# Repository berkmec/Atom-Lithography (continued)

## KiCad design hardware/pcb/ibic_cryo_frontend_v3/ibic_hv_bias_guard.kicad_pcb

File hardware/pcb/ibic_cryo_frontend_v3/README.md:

# IBIC Cryo Front-End v3 — Split 3-PCB KiCad 8 Kit & Real 100 K `ngspice` Verification

**BOM Coverage:** `S3.1-01`, `S3.1-02`, `S3.2-01`, `S3.2-02`, `S3.2-03`, `S3.2-04`, `S3.2-05`, `S3.2-06`, `S3.3-03`  
**Epistemic Status:** `M0/M1_DESIGN_ONLY` — `no_lab_measurement=true`, `no_physical_fab=true`, `iec61508_certified=false`, `semi_s2_certified=false`. All active semiconductors are `{Aday-COTS}` candidate parts.

## 1. Physically Split 3-PCB Kit (100% Physically Routed Pad-to-Pad; Closing #281 & #327)

Replaces the pre-layout monolithic netlist (`src/board/detector_frontend.*`, preserved read-only for v7.2 hash parity) with 3 physically split KiCad 8 boards verified by strict S-expression parsing, reconstructive schematic-to-PCB ERC, full geometric + pad-segment-via-zone Union-Find connectivity DRC (`0` unconnected items, `0` dangling tracks), controlled-impedance `Z0` (`±5%`), IPC-2221/IEC-61010 HV rules, real `ngspice-47`, and independent Python MNA:

| Board Slug | BOM IDs | Temp / Env | Stackup & Size | Comps / Nets | Routed / Unconn / Dangling | Segs / Vias | ERC / DRC | Key Features |
| :--- | :--- | :--- | :--- | :---: | :---: | :---: | :---: | :--- |
| `ibic_cold_csa_100k` | `S3.2-01, S3.1-01/02, S3.2-04/05` | `100 K` UHV (`10⁻⁹ mbar`) | 4L Rogers RO4350B (`ε_r=3.48`), `125×105 mm` | `130 / 56` | **`56/56` / `0` / `0`** | `725 / 225` | **`0 / 0`** | 8× `LTC6268IS8` CSA (exact S8 pinout: `1:~SHDN, 2:V+, 3:OUT, 4:V-, 5/8:GUARD_DRV, 6:-IN, 7:+IN`) + `0805` cryo thin-film `1 GΩ` `RF`, extended `In1/In2` keepouts (`x=34.0..55.2 mm`) & active `U_GRD_BOOT` guard follower (no `100 nF` AC-short), `G=+2` `50 Ω` coax drivers (`Z0=50.00 Ω`) |
| `ibic_warm_shaper_300k` | `S3.2-02, S3.2-06, S3.3-03` | `300 K` EMI Chassis | 4L Isola FR408HR (`ε_r=3.66`), `185×135 mm` | `217 / 116` | **`116/116` / `0` / `0`** | `1,373 / 350` | **`0 / 0`** | 16× `ADA4817-1ARDZ` (`SOIC-8-1EP`: `1:FB, 8:PD=VCCA, 9:EP=VSSA`), 8× `TLV3501AIDBVR` (exact TI SBOS321 DBV: `1:-IN, 2:V-, 3:+IN, 4:V+, 5:OUT, 6:SHDN=DGND`), 5× `MSOP-12-1EP` `LT3045EMSE` (`EP=GND`) / `LT3094EMSE` (`EP=VIN_N`), 100% `F.Cu` `50 Ω` `SHP_ADC`/`COUNT_HIT`/`COAX_IN` over solid `In1.Cu` `AGND`/`DGND` (`0` `B.Cu` `50 Ω` segments) |
| `ibic_hv_bias_guard` | `S3.2-03, S3.1-01/02` | `300 K` HV / Guard | 4L Rogers RO4350B (`ε_r=3.48`), `110×75 mm` | `38 / 21` | **`21/21` / `0` / `0`** | `170 / 32` | **`0 / 0`** | 3-stage RC `0–100 V` HV filter (`3× 10 kΩ / 1.0 µF` 200 V), extended `2.5×61 mm` milled `Edge.Cuts` air-slot enclosing `RHV_DIV_TOP`, non-chopper `AD8675ARZ` driven guard buffer + `100:1` HV sense monitor |

## 2. Real `ngspice-47` & Independent MNA Verification (`ibic_cryo_chain_100k.cir`)

Executed natively with `ngspice-47 -b` (zero PSpice `VALUE={}` / `PARAMS:` syntax, exit code `0`, `0` errors, `0` warnings) using `.temp -173.15` (`100 K`) on the cold CSA stage (with active guard bootstrap follower, `0805` thin-film `RF` parasitic C, and `±2.5 V` supply-rail saturation clamps) and per-resistor `temp=26.85` (`300 K`) on the warm ex-vacuum shaper & HV filter:

| Metric | `ngspice-47` Measured | Independent Python MNA / Exp127 Ref | Target / Spec | Status |
| :--- | :---: | :---: | :---: | :---: |
| Peak AC Transimpedance `Z_peak` | `647.44 MΩ` (`@ 7.34 kHz`) | MNA `647.44 MΩ` (`0.0001%` diff) | `< 1%` MNA parity | **PASS** |
| `5 keV ³¹P⁺` Shaper Peak `V_peak` (`341.7 e⁻`) | `10.834 mV` (`197.9 mV/fC`) | Exp127 `10.917 mV` | `10–12 mV` | **PASS** |
| `5 keV` Peaking Time `t_peak` | `1225.6 ns` (`1.226 µs`) | Exp127 `1218.4 ns` | `≈ 1.2 µs` | **PASS** |
| Buffered FMC PHA ADC Tap `V_adc` | `10.780 mV` | `0.50%` tracking vs `V_peak` | `< 2%` tracking | **PASS** |
| Integrated Noise `ENC` (`10 Hz – 50 MHz`) | **`27.94 e⁻ rms`** | Active guard bootstrap + `300 K` warm shaper & `50 Ω` coax link | `≤ 35 e⁻` | **PASS** |
| `TLV3501` Comparator `COUNT_HIT` | `3.251 V`, `5.20 µs` pulse (`0 V` DC baseline, `SHDN=DGND`) | `V_thr = 4.23 mV`, `3.3 mV` hys | Clean trigger & reset | **PASS** |
| `S3.2-03` 3-Stage HV Filter `@ 100 kHz` | **`-227.86 dB`** (w/ `100 mΩ` ESR, `2 nH` ESL) | MNA `-227.86 dB` (`0.001 dB` diff) | `> 100 dB` (`< -100 dB`) | **PASS** |
| `S3.2-03` HV Filter Integrated Thermal Noise | **`0.142 µVrms`** | — | `< 10 µVrms` | **PASS** |
| Cold CSA `CSA_SUM` Stray Capacitance Budget | `0.109 pF` active bootstrapped (`0.775 pF` passive ref) | `In1/In2` keepout `x=34.0..55.2 mm` | `< 0.15 pF` | **PASS** |

## 3. Reproducibility

```bash
PYTHONPATH=.:src python -B hardware/pcb/ibic_cryo_frontend_v3/build_ibic_v3.py
PYTHONPATH=.:src pytest tests/test_pcb_kernel_and_ibic.py -v -p no:cacheprovider
```

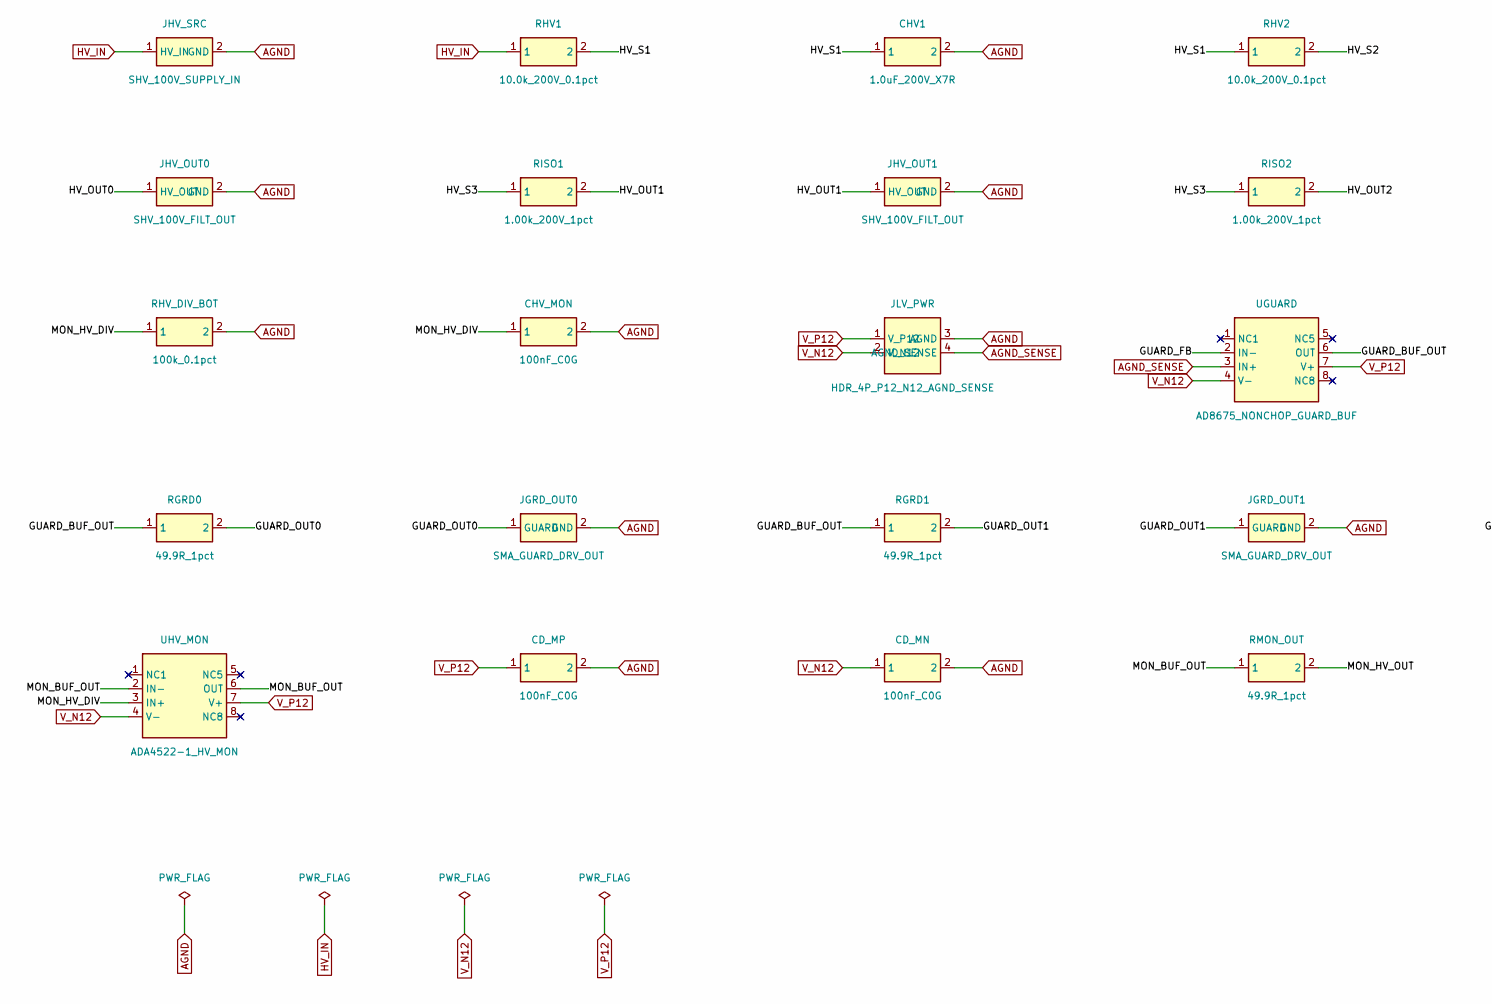
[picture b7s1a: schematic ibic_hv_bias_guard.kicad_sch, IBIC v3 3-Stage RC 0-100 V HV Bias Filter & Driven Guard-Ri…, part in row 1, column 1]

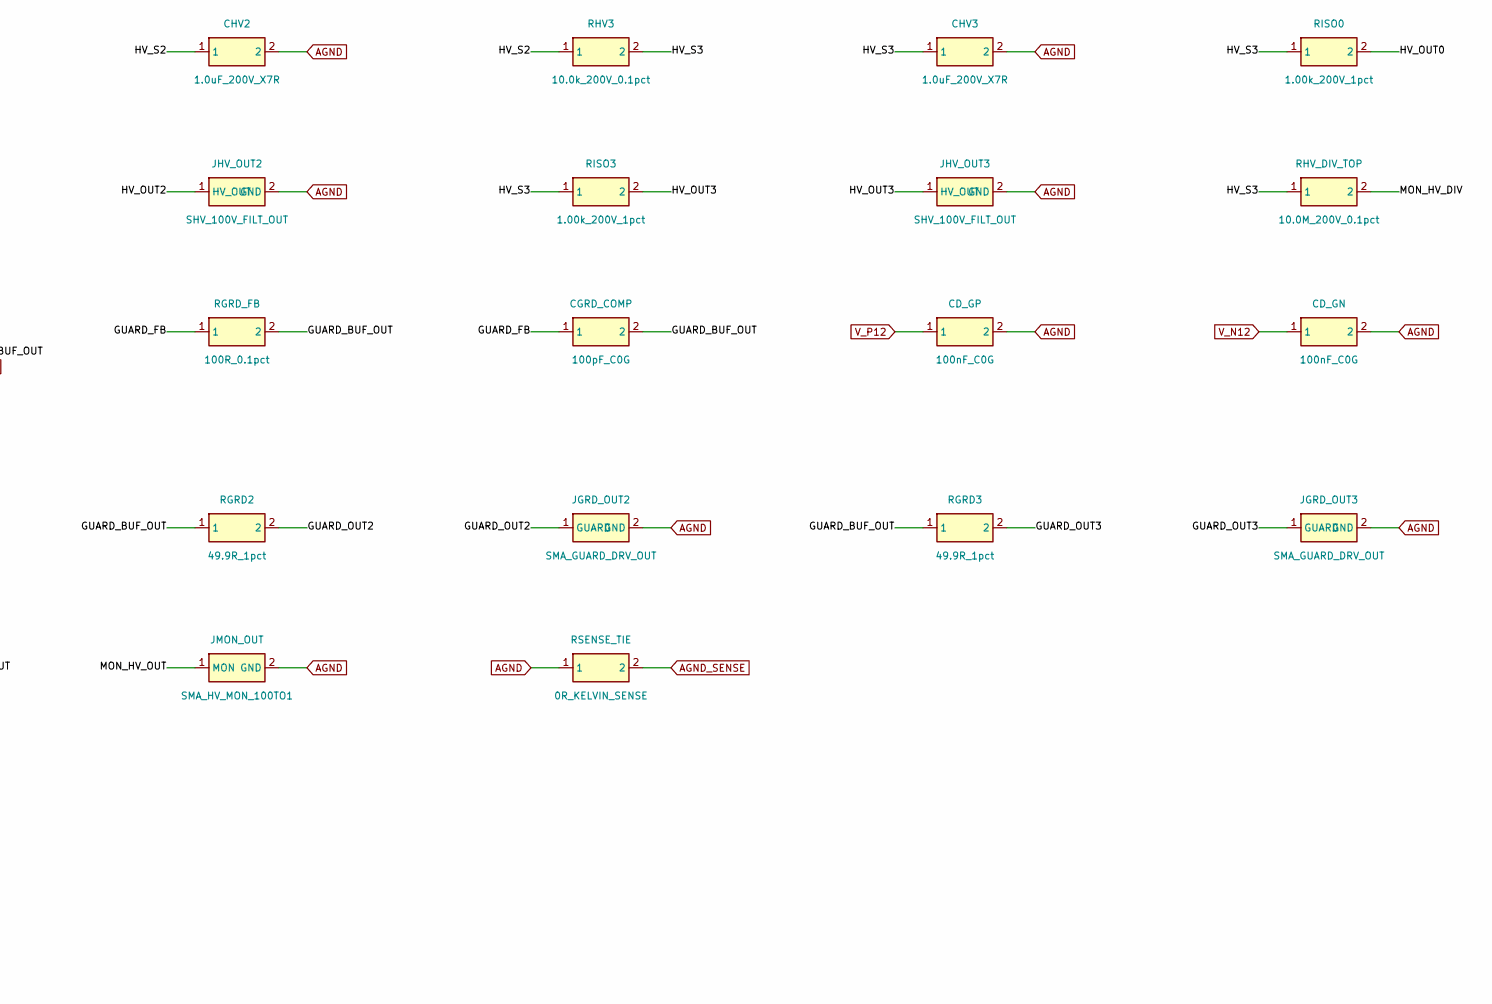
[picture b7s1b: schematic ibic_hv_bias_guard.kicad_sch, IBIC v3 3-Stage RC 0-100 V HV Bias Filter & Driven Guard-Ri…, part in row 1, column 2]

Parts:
CD_GN: 100nF_C0G; C_0603_1608Metric; MPN 100nF_C0G
CD_GP: 100nF_C0G; C_0603_1608Metric; MPN 100nF_C0G
CD_MN: 100nF_C0G; C_0603_1608Metric; MPN 100nF_C0G
CD_MP: 100nF_C0G; C_0603_1608Metric; MPN 100nF_C0G
CGRD_COMP: 100pF_C0G; C_0603_1608Metric; MPN 100pF_C0G
CHV1, CHV2, CHV3: 1.0uF_200V_X7R; C_1210_3225Metric; MPN 1.0uF_200V_X7R
CHV_MON: 100nF_C0G; C_0603_1608Metric; MPN 100nF_C0G
JGRD_OUT0, JGRD_OUT1, JGRD_OUT2, JGRD_OUT3: SMA_GUARD_DRV_OUT; SMA_EdgeMount; MPN SMA_GUARD_DRV_OUT
JHV_OUT0, JHV_OUT1, JHV_OUT2, JHV_OUT3: SHV_100V_FILT_OUT; SHV_Amphenol_HV; MPN SHV_100V_FILT_OUT
JHV_SRC: SHV_100V_SUPPLY_IN; SHV_Amphenol_HV; MPN SHV_100V_SUPPLY_IN
JLV_PWR: HDR_4P_P12_N12_AGND_SENSE; HDR_1x4_2.54mm; MPN HDR_4P_P12_N12_AGND_SENSE
JMON_OUT: SMA_HV_MON_100TO1; SMA_EdgeMount; MPN SMA_HV_MON_100TO1
RGRD0, RGRD1, RGRD2, RGRD3: 49.9R_1pct; R_0603_1608Metric; MPN 49.9R_1pct
RGRD_FB: 100R_0.1pct; R_0603_1608Metric; MPN 100R_0.1pct
RHV1, RHV2, RHV3: 10.0k_200V_0.1pct; R_1206_3216Metric; MPN 10.0k_200V_0.1pct
RHV_DIV_BOT: 100k_0.1pct; R_0805_2012Metric; MPN 100k_0.1pct
RHV_DIV_TOP: 10.0M_200V_0.1pct; R_2512_6332Metric; MPN 10.0M_200V_0.1pct
RISO0, RISO1, RISO2, RISO3: 1.00k_200V_1pct; R_1206_3216Metric; MPN 1.00k_200V_1pct
RMON_OUT: 49.9R_1pct; R_0603_1608Metric; MPN 49.9R_1pct
RSENSE_TIE: 0R_KELVIN_SENSE; R_0603_1608Metric; MPN 0R_KELVIN_SENSE
UGUARD: AD8675_NONCHOP_GUARD_BUF; SOIC-8_3.9x4.9mm_P1.27mm; MPN AD8675ARZ
UHV_MON: ADA4522-1_HV_MON; SOIC-8_3.9x4.9mm_P1.27mm; MPN ADA4522-1ARZ

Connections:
AGND: CD_GN.2, CD_GP.2, CD_MN.2, CD_MP.2, CHV1.2, CHV2.2, CHV3.2, CHV_MON.2, JGRD_OUT0.2 (GND), JGRD_OUT1.2 (GND), JGRD_OUT2.2 (GND), JGRD_OUT3.2 (GND), JHV_OUT0.2 (GND), JHV_OUT1.2 (GND), JHV_OUT2.2 (GND), JHV_OUT3.2 (GND), JHV_SRC.2 (GND), JLV_PWR.3 (AGND), JMON_OUT.2 (GND), RHV_DIV_BOT.2, RSENSE_TIE.1
AGND_SENSE: JLV_PWR.4 (AGND_SENSE), RSENSE_TIE.2, UGUARD.3 (IN+)
GUARD_BUF_OUT: CGRD_COMP.2, RGRD0.1, RGRD1.1, RGRD2.1, RGRD3.1, RGRD_FB.2, UGUARD.6 (OUT)
GUARD_FB: CGRD_COMP.1, RGRD_FB.1, UGUARD.2 (IN-)
GUARD_OUT0: JGRD_OUT0.1 (GUARD), RGRD0.2
GUARD_OUT1: JGRD_OUT1.1 (GUARD), RGRD1.2
GUARD_OUT2: JGRD_OUT2.1 (GUARD), RGRD2.2
GUARD_OUT3: JGRD_OUT3.1 (GUARD), RGRD3.2
HV_IN: JHV_SRC.1 (HV_IN), RHV1.1
HV_OUT0: JHV_OUT0.1 (HV_OUT), RISO0.2
HV_OUT1: JHV_OUT1.1 (HV_OUT), RISO1.2
HV_OUT2: JHV_OUT2.1 (HV_OUT), RISO2.2
HV_OUT3: JHV_OUT3.1 (HV_OUT), RISO3.2
HV_S1: CHV1.1, RHV1.2, RHV2.1
HV_S2: CHV2.1, RHV2.2, RHV3.1
HV_S3: CHV3.1, RHV3.2, RHV_DIV_TOP.1, RISO0.1, RISO1.1, RISO2.1, RISO3.1
MON_BUF_OUT: RMON_OUT.1, UHV_MON.2 (IN-), UHV_MON.6 (OUT)
MON_HV_DIV: CHV_MON.1, RHV_DIV_BOT.1, RHV_DIV_TOP.2, UHV_MON.3 (IN+)
MON_HV_OUT: JMON_OUT.1 (MON), RMON_OUT.2
V_N12: CD_GN.1, CD_MN.1, JLV_PWR.2 (V_N12), UGUARD.4 (V-), UHV_MON.4 (V-)
V_P12: CD_GP.1, CD_MP.1, JLV_PWR.1 (V_P12), UGUARD.7 (V+), UHV_MON.7 (V+)

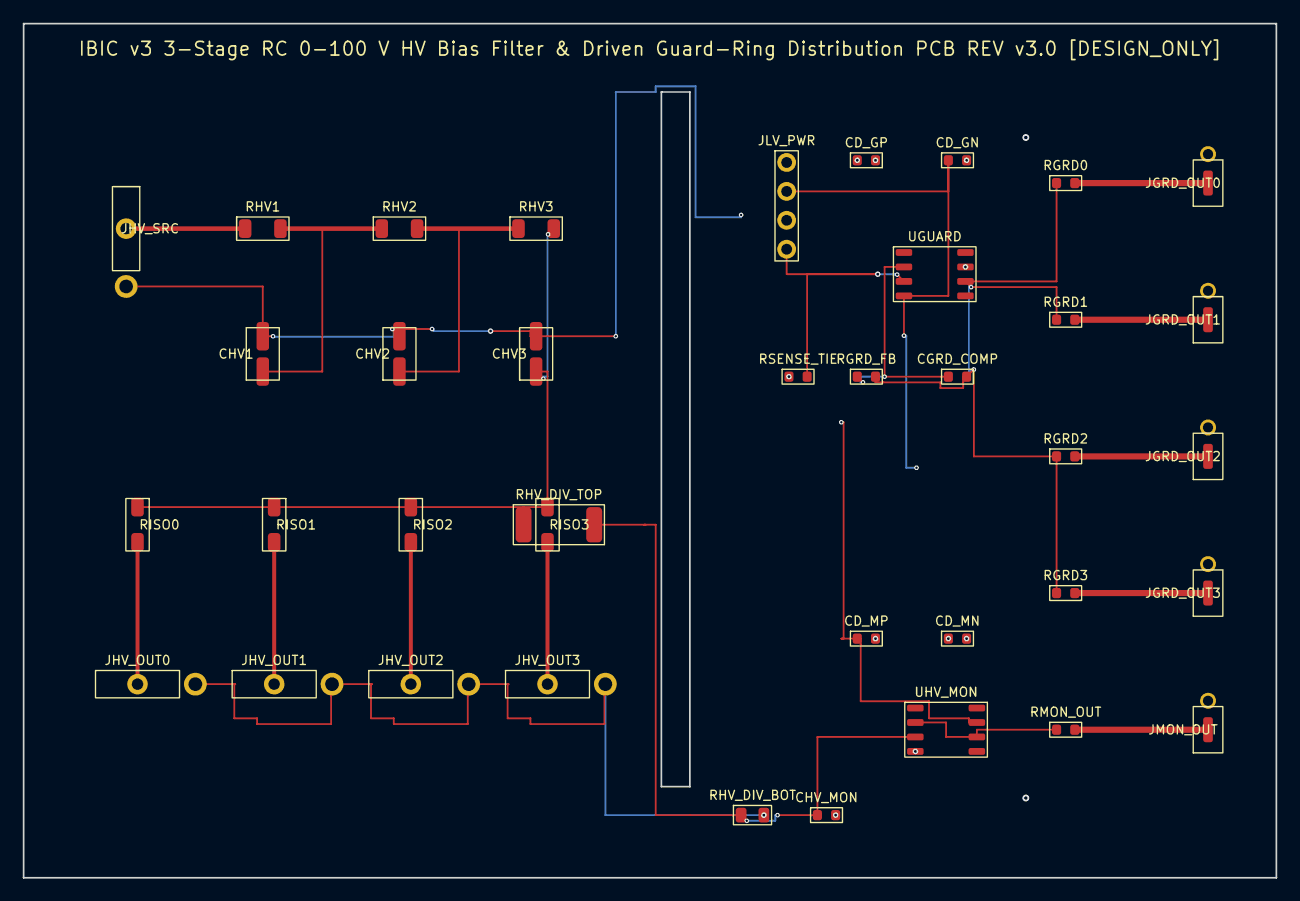
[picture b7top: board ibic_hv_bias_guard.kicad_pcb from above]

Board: 4 copper layers, 110.0 x 75.0 mm, 38 parts (0 on the bottom side), 21 nets.

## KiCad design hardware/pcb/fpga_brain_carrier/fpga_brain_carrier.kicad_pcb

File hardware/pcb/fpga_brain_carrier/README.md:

# FPGA Brain Carrier PCB (`XC7K325T-2FFG900` + `ZU48DR` 2U Rack ICD) & Live `ngspice-47` PDN Verification

**BOM Coverage:** `S3.3-01`, `S3.3-02`, `S3.3-04`, `S1.4-03`, `S4.5-03`, `S6.9-04`, plus `S6.11-01` (`ZU48DR` 2U Rack ICD Ref), `S3.3-03` (`FMC HPC` ADC port), `S7.4-01` (`10 MHz` Rb), `S7.4-02` (White Rabbit trigger).  
**Epistemic Status:** `M0/M1_DESIGN_ONLY` — `no_lab_measurement=true`, `no_physical_fab=true`, `iec61508_certified=false`, `semi_s2_certified=false`. All active semiconductors are `{Aday-COTS}` candidates.

## 1. Yosys-Grounded FPGA Sizing & `ZU48DR` 2U Rack ICD

Directly sized to real Yosys pre-P&R cell counts (`results/exp149_*/yosys_*_stat.json` and `results/stage2_rtl_verification/yosys_xc7_stat.json`):

| RTL Target / Device | LUTs | FFs | BRAM (`BRAM36-eq`) | DSP / MULT | Notes |
| :--- | ---: | ---: | ---: | ---: | :--- |
| `boed_q16_core` (`ecp5` Yosys) | `3,871` | `4,448` | `12 DP16KD` (`6.0`) | `106 MULT18X18D` | Exceeds `LFE5U-45F` (72 DSP) |
| `boed_q16_core` (`xc7` Yosys) | `5,467` | `3,080` | `12 RAMB18E1` (`6.0`) | `99 DSP48E1` | Single-channel BOED core |
| `boed_top_16ch` (`xcup` Yosys) | `102,886` | `59,157` | `192 RAMB18E2` (`96.0`) | `1,584 DSP48E2` | `24.2%` LUT / `37.1%` DSP on `ZU48DR` |
| `fpga_top_machine_ctrl` (`xc7`, BOED + all 6 controllers) | `14,252` | `10,517` | `12 RAMB18E1` (`6.0`) | `124 DSP48E1` | Full unified control brain |
| **Carrier `XC7K325T-2FFG900` Capacity** | **`203,800`** (`14.3×`) | **`407,600`** (`38.8×`) | **`445`** (`74.2×`) | **`840`** (**`6.77×`**) | **`> 4×` headroom across all resources** |
| **`S6.11-01` `ZU48DR` 2U Rack ICD Ref** | `2× XCZU48DR-2FFVG1517E` | `32` Direct-RF chains | `87.96 W` @ `300 K` (`0 W` cryo) | `250 MHz` (`2.336 µs`/step) | `482.6×520×88.9 mm`, `11.50 kg` |

## 2. 8-Layer Isola FR408HR Board Architecture (`fpga_brain_carrier.{kicad_sch,kicad_pcb}`)

- **Dimensions & Stackup:** `230 × 170 mm`, **`8` copper layers** (`SIG1-GND-SIG2-PWR-GND-SIG3-GND-SIG4`), `1.534 mm` total thickness, Isola FR408HR (`ε_r = 3.66`, `tanδ = 0.0092`). `In3.Cu` (`VCCINT_1V0` PWR) and `In4.Cu` (`GND2`) use `2 oz` (`0.070 mm`) copper over a `0.100 mm` thin core for low planar spreading inductance.
- **Controlled Impedance (`104 / 104` DRC checks PASS across all routed segments, `±5%`):**
  - `50 Ω SE` microstrip (`F.Cu`/`B.Cu`): `w = 0.2500 mm` → `Z0 = 50.00 Ω` on `10 MHz` Rb & White Rabbit SMA inputs.
  - `50 Ω SE` stripline (`In2.Cu`/`In5.Cu`): `w = 0.1726 mm` → `Z0 = 50.00 Ω` on `DDR4 DQ0..DQ3`.
  - `100 Ω diff` edge-coupled microstrip (`w = 0.2096 mm`, `s = 0.22 mm` → `Z_diff = 100.00 Ω`) & stripline (`In2.Cu`/`In5.Cu`, `w = 0.1421 mm`, `s = 0.22 mm` → `Z_diff = 100.00 Ω`): coupled `250/100/125 MHz` LVDS clocks with `B.Cu` backside via-in-pad `100 Ω` termination beneath `XC7K325T`, planar fly-by `DDR4 CK`, `FMC HPC` ADC lanes, isolated IBIC/Blanker LVDS ports, and `1000BASE-T` MDI pairs.
- **Subsystems:** `12 V` protected bus → `LM3880` power sequencer → `TPS546D24A` (`1.0 V VCCINT @ 15 A` + `64`-cap 5-decade PDN bank), `1.8 V`, `1.2 V DDR4 + 0.6 V TPS51200 VTT`, `2.5 V LVDS`, `3.3 V IO`, `2× LT3045` (`1.0 V/1.2 V` MGT); `LMK04828` dual-loop jitter cleaner + `CVHD-950` `100 MHz` VCXO; `2 GB` DDR4 (`2× MT40A512M16LY`), `256 Mb` QSPI NOR (`MT25QU256ABA`); `FMC HPC` (`ASP-134488-01`); `4×` isolated LVDS/SPI ports (`ADN4654`/`ADuM141D`: IBIC, Blanker, HV-DAC, AOM/Pyro + `1oo2D` Interlock); `DP83867IR` `1000BASE-T` GbE; `FT232HL` USB-UART; `14-pin` JTAG.
- **Strict EDA & Physical Copper Connectivity Verification:** `139` components, `126` nets, **`routed = 126 / 126` (`100%` pad-to-pad)**, **`unconnected_items = 0`**, **`track_dangling_count = 0`**, `1,625` copper segments, `468` vias, **`0` ERC errors**, **`0` DRC errors**, `SCH ↔ PCB` netlist parity PASS.

## 3. Live `ngspice-47` PDN AC Impedance & `5 A` Transient Verification (`fpga_pdn_1v0.cir`)

Executed natively with `ngspice-47 -b` (exit `0`, `0` errors, `0` warnings) modeling realistic VRM closed-loop impedance (`1.0 mΩ`, `14 nH`), 5-decade bulk+MLCC ESR/ESL (`4× 470 µF`, `8× 47 µF`, `12× 4.7 µF`, `16× 470 nF`, `24× 100 nF`), 2 oz plane spreading inductance, and `XC7K325T` FFG900 package/die capacitance:

| Metric | `ngspice-47` Measured | Independent Python MNA | Target / Spec | Status |
| :--- | :---: | :---: | :---: | :---: |
| Peak `|Z_PDN(f)|` (`100 Hz – 20 MHz`) | **`4.1604 mΩ`** (`@ 30.43 kHz`) | `4.1604 mΩ` (`0.0002%` diff) | `< 10 mΩ` | **PASS** |
| `|Z_PDN|` at `100 Hz` / `10 kHz` / `1 MHz` | `2.000` / `2.366` / `1.782 mΩ` | `2.000` / `2.366` / `1.782 mΩ` | `< 10 mΩ` | **PASS** |
| `|Z_PDN|` at `10 MHz` / `20 MHz` | `2.914` / **`3.210 mΩ`** | `2.913` / `3.209 mΩ` | `< 10 mΩ` | **PASS** |
| Transient `5 A` Load-Step Droop (`1→6 A`, `50 ns`) | **`16.21 mV`** (`1.621%`) | — | `< 30 mV` (`±3%`) | **PASS** |
| Transient `5 A` Load-Release Overshoot | **`6.23 mV`** (`0.623%`) | — | `< 30 mV` (`±3%`) | **PASS** |

## 4. Reproducibility

```bash
PYTHONPATH=.:src python -B hardware/pcb/fpga_brain_carrier/build_fpga_carrier.py
PYTHONPATH=.:src pytest tests/test_pcb_fpga_blanker_cryo.py -v -p no:cacheprovider
```

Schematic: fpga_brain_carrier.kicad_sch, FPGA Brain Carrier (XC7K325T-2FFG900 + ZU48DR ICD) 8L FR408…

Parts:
C_1V0_OUT, C_1V2_OUT, C_1V8_OUT, C_2V5_OUT, C_3V3_OUT: 47uF_6V3_X5R; C_1206_3216Metric; MPN 47uF_6V3_X5R
C_BST_1V2, C_BST_1V8, C_BST_2V5, C_BST_3V3: 100nF_0603; C_0603_1608Metric; MPN 100nF_0603
C_IN12_1: 100uF_25V_POLY; C_1210_3225Metric; MPN 100uF_25V_POLY
C_IN12_2: 10uF_25V_X7R; C_0805_2012Metric; MPN 10uF_25V_X7R
C_LF1: 22nF_C0G; C_0603_1608Metric; MPN 22nF_C0G
C_OUT_MGT0, C_OUT_MGT1: 10uF_C0G; C_0805_2012Metric; MPN 10uF_C0G
C_PDN_4U7_1, C_PDN_4U7_2, C_PDN_4U7_3, C_PDN_4U7_4, C_PDN_4U7_5, C_PDN_4U7_6, C_PDN_4U7_7, C_PDN_4U7_8, C_PDN_4U7_9, C_PDN_4U7_10, C_PDN_4U7_11, C_PDN_4U7_12: 4.7uF_6V3_X7R_0805; C_0805_2012Metric; MPN 4.7uF_6V3_X7R_0805
C_PDN_47U_1, C_PDN_47U_2, C_PDN_47U_3, C_PDN_47U_4, C_PDN_47U_5, C_PDN_47U_6, C_PDN_47U_7, C_PDN_47U_8: 47uF_6V3_X5R_1206; C_1206_3216Metric; MPN 47uF_6V3_X5R_1206
C_PDN_100N_1, C_PDN_100N_2, C_PDN_100N_3, C_PDN_100N_4, C_PDN_100N_5, C_PDN_100N_6, C_PDN_100N_7, C_PDN_100N_8, C_PDN_100N_9, C_PDN_100N_10, C_PDN_100N_11, C_PDN_100N_12, C_PDN_100N_13, C_PDN_100N_14, C_PDN_100N_15, C_PDN_100N_16, C_PDN_100N_17, C_PDN_100N_18, C_PDN_100N_19, C_PDN_100N_20, C_PDN_100N_21, C_PDN_100N_22, C_PDN_100N_23, C_PDN_100N_24: 100nF_10V_X7R_0402; C_0402_1005Metric; MPN 100nF_10V_X7R_0402
C_PDN_470N_1, C_PDN_470N_2, C_PDN_470N_3, C_PDN_470N_4, C_PDN_470N_5, C_PDN_470N_6, C_PDN_470N_7, C_PDN_470N_8, C_PDN_470N_9, C_PDN_470N_10, C_PDN_470N_11, C_PDN_470N_12, C_PDN_470N_13, C_PDN_470N_14, C_PDN_470N_15, C_PDN_470N_16: 470nF_10V_X7R_0603; C_0603_1608Metric; MPN 470nF_10V_X7R_0603
C_PDN_BULK1, C_PDN_BULK2, C_PDN_BULK3, C_PDN_BULK4: 470uF_2V5_POSCAP_9mR; C_1210_3225Metric; MPN 470uF_2V5_POSCAP_9mR
C_RST: 100nF_0603; C_0603_1608Metric; MPN 100nF_0603
C_SS_1V2, C_SS_1V8, C_SS_2V5, C_SS_3V3: 10nF_0603; C_0603_1608Metric; MPN 10nF_0603
C_STBY_3V3: 10uF_10V_C0G; C_0603_1608Metric; MPN 10uF_10V_C0G
C_VR5_1V2, C_VR5_1V8, C_VR5_2V5, C_VR5_3V3: 1.0uF_0603; C_0603_1608Metric; MPN 1.0uF_0603
C_VTT_OUT: 10uF_6V3_X5R; C_0805_2012Metric; MPN 10uF_6V3_X5R
D_DONE: LED_GRN_0603; LED_0603_1608Metric; MPN LED_GRN_0603
D_TVS1: SMBJ15A_TVS; R_1206_3216Metric; MPN SMBJ15A_TVS
F1: 10A_FAST_2410; R_1206_3216Metric; MPN 10A_FAST_2410
J_ETH: RJ45_MAGJACK_1GBE; HDR_2x4_2.54mm; MPN RJ45_MAGJACK_1GBE
J_FMC_HPC: ASP-134488-01_FMC_HPC_400P; FMC_HPC_400P_10x40_P1.27mm; MPN ASP-134488-01
J_IL_1OO2D_AUX: HDR_1x4_1OO2D_CHB_ISO; HDR_1x4_2.54mm; MPN HDR_1x4_1OO2D_CHB_ISO
J_JTAG: XILINX_JTAG_14P_HDR2X7; HDR_2x7_2.00mm; MPN XILINX_JTAG_14P_HDR2X7
J_PORT_AOM_IL: HDR_2x6_ISO_AOM_1OO2D_RTL; HDR_2x6_2.54mm; MPN HDR_2x6_ISO_AOM_1OO2D_RTL
J_PORT_BLK: HDR_2x6_ISO_BLK; HDR_2x6_2.54mm; MPN HDR_2x6_ISO_BLK
J_PORT_HVDAC: HDR_2x6_ISO_HVDAC_RTL; HDR_2x6_2.54mm; MPN HDR_2x6_ISO_HVDAC_RTL
J_PORT_IBIC: HDR_2x6_ISO_IBIC; HDR_2x6_2.54mm; MPN HDR_2x6_ISO_IBIC
J_PWR12V: MOLEX_MINIFIT_12V_15A; HDR_1x4_2.54mm; MPN MOLEX_MINIFIT_12V_15A
J_RB_10M: SMA_10MHZ_RB_REF; SMA_EdgeMount; MPN SMA_10MHZ_RB_REF
J_USB: USB_C_UART_CONSOLE; HDR_1x4_2.54mm; MPN USB_C_UART_CONSOLE
J_WR_TRIG: SMA_WHITE_RABBIT_TRIG; SMA_EdgeMount; MPN SMA_WHITE_RABBIT_TRIG
L_1V0: 0.47uH_20A; L_1210_3225Metric; MPN 0.47uH_20A
L_1V2, L_1V8: 2.2uH_6A; L_1210_3225Metric; MPN 2.2uH_6A
L_2V5: 3.3uH_4A; L_1210_3225Metric; MPN 3.3uH_4A
L_3V3: 3.3uH_6A; L_1210_3225Metric; MPN 3.3uH_6A
R_DDR_VTT1, R_DDR_VTT2: 39R_0603; R_0603_1608Metric; MPN 39R_0603
R_DONE: 470R_0603; R_0603_1608Metric; MPN 470R_0603
R_FBB_1V2, R_FBB_1V8, R_FBB_2V5, R_FBB_3V3: 10.0k_0.1pct; R_0603_1608Metric; MPN 10.0k_0.1pct
R_FBT_1V2: 5.69k_0.1pct; R_0603_1608Metric; MPN 5.69k_0.1pct
R_FBT_1V8: 13.5k_0.1pct; R_0603_1608Metric; MPN 13.5k_0.1pct
R_FBT_2V5: 22.6k_0.1pct; R_0603_1608Metric; MPN 22.6k_0.1pct
R_FBT_3V3: 33.2k_0.1pct; R_0603_1608Metric; MPN 33.2k_0.1pct
R_INIT: 4.7k_0603; R_0603_1608Metric; MPN 4.7k_0603
R_LF1: 1.2k_0603; R_0603_1608Metric; MPN 1.2k_0603
R_PGOOD_PU: 10.0k_1pct; R_0603_1608Metric; MPN 10.0k_1pct
R_RB_50: 49.9R_0.1pct; R_0603_1608Metric; MPN 49.9R_0.1pct
R_RST: 10k_0603; R_0603_1608Metric; MPN 10k_0603
R_SEQ_EN: 30.1k_0.1pct_UVLO; R_0603_1608Metric; MPN 30.1k_0.1pct_UVLO
R_SEQ_EN_B: 10.0k_0.1pct_UVLO; R_0603_1608Metric; MPN 10.0k_0.1pct_UVLO
R_SET_MGT0: 10.0k_0.1pct; R_0603_1608Metric; MPN 10.0k_0.1pct
R_SET_MGT1: 12.0k_0.1pct; R_0603_1608Metric; MPN 12.0k_0.1pct
R_TERM_100M, R_TERM_125M, R_TERM_250M: 100R_0.1pct_0402; R_0402_1005Metric; MPN 100R_0.1pct_0402
R_TERM_FMC_CLK: 100R_0.1pct_0402; R_0402_1005Metric; MPN 100R_0.1pct_0402
R_TERM_FMC_D0, R_TERM_FMC_D1: 100R_0.1pct_0402; R_0402_1005Metric; MPN 100R_0.1pct_0402
R_TERM_IBIC_HIT: 100R_0.1pct_0402; R_0402_1005Metric; MPN 100R_0.1pct_0402
R_VTT_REFIN_B: 10.0k_0.1pct_REFIN; R_0603_1608Metric; MPN 10.0k_0.1pct_REFIN
R_VTT_REFIN_T: 10.0k_0.1pct_REFIN; R_0603_1608Metric; MPN 10.0k_0.1pct_REFIN
R_WR_50: 49.9R_0.1pct; R_0603_1608Metric; MPN 49.9R_0.1pct
U1: XC7K325T-2FFG900; Xilinx_FFG900_31x31mm_P1.0mm; MPN XC7K325T-2FFG900I
U_CLK: LMK04828BISQ_WQFN64; QFN-64-1EP_9x9mm_P0.5mm_EP7.15x7.15mm; MPN LMK04828BISQ
U_DDR4_A: MT40A512M16LY_FBGA96_A; FBGA-96_9x13mm_P0.8mm; MPN MT40A512M16LY-062E
U_DDR4_B: MT40A512M16LY_FBGA96_B; FBGA-96_9x13mm_P0.8mm; MPN MT40A512M16LY-062E
U_GBE: DP83867IR_VQFN48_RGMII; QFN-48-1EP_7x7mm_P0.5mm_EP5.1x5.1mm; MPN DP83867IRRGZR
U_ISO_AOM_IL: ADUM141D_ISO_AOM_SPI; SOIC-16W_7.5x10.3mm_P1.27mm; MPN ADUM141DBRWZ
U_ISO_AOM_IL2: ADUM141D_ISO_1OO2D_WDT; SOIC-16W_7.5x10.3mm_P1.27mm; MPN ADUM141DBRWZ
U_ISO_BLK: ADN4654_ISO_LVDS_BLANKER; SOIC-16W_7.5x10.3mm_P1.27mm; MPN ADN4654BRWZ
U_ISO_BLK_CTRL: ADUM141D_ISO_BLK_CTRL; SOIC-16W_7.5x10.3mm_P1.27mm; MPN ADUM141DBRWZ
U_ISO_HVDAC: ADUM141D_ISO_SPI_HVDAC; SOIC-16W_7.5x10.3mm_P1.27mm; MPN ADUM141DBRWZ
U_ISO_HVDAC2: ADUM141D_ISO_HVDAC_CTRL; SOIC-16W_7.5x10.3mm_P1.27mm; MPN ADUM141DBRWZ
U_ISO_IBIC: ADN4654_ISO_LVDS_IBIC; SOIC-16W_7.5x10.3mm_P1.27mm; MPN ADN4654BRWZ
U_ISO_IBIC_SPI: ADUM141D_ISO_IBIC_SPI; SOIC-16W_7.5x10.3mm_P1.27mm; MPN ADUM141DBRWZ
U_ISO_IL_AUX: ADUM141D_ISO_1OO2D_CHB; SOIC-16W_7.5x10.3mm_P1.27mm; MPN ADUM141DBRWZ
U_LDO_MGT1V0: LT3045EDD_MGTAVCC_1V0; DFN-10-1EP_3x3mm_P0.5mm_EP1.55x2.48mm; MPN LT3045EDD
U_LDO_MGT1V2: LT3045EDD_MGTAVTT_1V2; DFN-10-1EP_3x3mm_P0.5mm_EP1.55x2.48mm; MPN LT3045EDD
U_LDO_STBY_3V3: ADP7142AUJZ-3.3_STBY; TSOT-23-5; MPN ADP7142AUJZ-3.3
U_QSPI: MT25QU256ABA_256Mb; SOIC-8_3.9x4.9mm_P1.27mm; MPN MT25QU256ABA1EW7
U_SEQ1: LM3880MF-1AA_SOT23_6; SOT-23-6; MPN LM3880MF-1AA
U_UART: FT232HL_LQFP48_UART; LQFP-48_7x7mm_P0.5mm; MPN FT232HL-REEL
U_VR_1V0: TPS546D24A_QFN40_1V0_15A; TQFN-40-1EP_5x7mm_P0.5mm; MPN TPS546D24ARVFR
U_VR_1V2: TPS54527_1V2_DDR; SOIC-8-1EP_3.9x4.9mm_P1.27mm_EP2.29x3mm; MPN TPS54527DDAR
U_VR_1V8: TPS54527_1V8_4A; SOIC-8-1EP_3.9x4.9mm_P1.27mm_EP2.29x3mm; MPN TPS54527DDAR
U_VR_2V5: TPS54327_2V5_LVDS; SOIC-8-1EP_3.9x4.9mm_P1.27mm_EP2.29x3mm; MPN TPS54327DDAR
U_VR_3V3: TPS54527_3V3_IO; SOIC-8-1EP_3.9x4.9mm_P1.27mm_EP2.29x3mm; MPN TPS54527DDAR
U_VTT_0V6: TPS51200DRCR_0V6_VTT; VSON-10-1EP_3x3mm_P0.5mm; MPN TPS51200DRCR
Y_VCXO: CVHD-950_100MHZ_VCXO; CVHD-950_9x14mm; MPN CVHD-950-100.000

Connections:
AOM_CS_N: U1.H5 (AOM_CS_N), U_ISO_AOM_IL.6 (A4)
AOM_RF_EN: U1.H6 (AOM_RF_EN), U_ISO_AOM_IL2.3 (A1)
AOM_SPI_MISO: U1.H4 (AOM_SPI_MISO), U_ISO_AOM_IL.5 (A3)
AOM_SPI_MOSI: U1.H3 (AOM_SPI_MOSI), U_ISO_AOM_IL.4 (A2)
AOM_SPI_SCK: U1.H2 (AOM_SPI_SCK), U_ISO_AOM_IL.3 (A1)
BLK_CLK_N: U1.G4 (BLK_CLK_N), U_ISO_BLK.6 (A4)
BLK_CLK_P: U1.G3 (BLK_CLK_P), U_ISO_BLK.5 (A3)
BLK_SAFE_FORCE: U1.G6 (BLK_SAFE_FORCE), U_ISO_BLK_CTRL.4 (A2)
BLK_START: U1.G5 (BLK_START), U_ISO_BLK_CTRL.3 (A1)
BLK_TX_N: U1.G2 (BLK_TX_N), U_ISO_BLK.4 (A2)
BLK_TX_P: U1.G1 (BLK_TX_P), U_ISO_BLK.3 (A1)
BST_1V2: C_BST_1V2.1, U_VR_1V2.7 (VBST)
BST_1V8: C_BST_1V8.1, U_VR_1V8.7 (VBST)
BST_2V5: C_BST_2V5.1, U_VR_2V5.7 (VBST)
BST_3V3: C_BST_3V3.1, U_VR_3V3.7 (VBST)
CLK_10M_RB: J_RB_10M.1 (CLK10M), R_RB_50.1, U_CLK.4 (CLKIN0_10M)
CLK_100M_N: R_TERM_100M.2, U1.C4 (CLK_100M_N), U_CLK.39 (CLK100_N)
CLK_100M_P: R_TERM_100M.1, U1.C3 (CLK_100M_P), U_CLK.40 (CLK100_P)
CLK_125M_N: R_TERM_125M.2, U1.C2 (CLK_125M_N), U_CLK.43 (CLK125_N)
CLK_125M_P: R_TERM_125M.1, U1.C1 (CLK_125M_P), U_CLK.44 (CLK125_P)
CLK_250M_N: R_TERM_250M.2, U1.C6 (CLK_250M_N), U_CLK.35 (CLK250_N)
CLK_250M_P: R_TERM_250M.1, U1.C5 (CLK_250M_P), U_CLK.36 (CLK250_P)
CLK_LOCKED: U1.C8 (CLK_LOCKED), U_CLK.20 (PLL_LOCK)
DDR_A0: R_DDR_VTT1.1, U1.D7 (DDR_A0), U_DDR4_A.37 (A0), U_DDR4_B.37 (A0)
DDR_A1: R_DDR_VTT2.1, U1.D8 (DDR_A1), U_DDR4_A.43 (A1), U_DDR4_B.43 (A1)
DDR_CKE: U1.D10 (DDR_CKE), U_DDR4_A.55 (CKE), U_DDR4_B.55 (CKE)
DDR_CK_N: U1.C10 (DDR_CK_N), U_DDR4_A.12 (CK_N), U_DDR4_B.12 (CK_N)
DDR_CK_P: U1.C9 (DDR_CK_P), U_DDR4_A.6 (CK_P), U_DDR4_B.6 (CK_P)
DDR_CS_N: U1.D1 (DDR_CS_N), U_DDR4_A.13 (CS_N), U_DDR4_B.13 (CS_N)
DDR_DQ0: U1.D3 (DDR_DQ0), U_DDR4_A.25 (DQ0)
DDR_DQ1: U1.D4 (DDR_DQ1), U_DDR4_A.31 (DQ1)
DDR_DQ2: U1.D5 (DDR_DQ2), U_DDR4_B.25 (DQ0)
DDR_DQ3: U1.D6 (DDR_DQ3), U_DDR4_B.31 (DQ1)
DDR_ODT: U1.D9 (DDR_ODT), U_DDR4_A.49 (ODT), U_DDR4_B.49 (ODT)
DDR_WE_N: U1.D2 (DDR_WE_N), U_DDR4_A.19 (WE_N), U_DDR4_B.19 (WE_N)
EN_1V0: U_SEQ1.6 (FLAG1), U_VR_1V0.4 (EN_UVLO)
EN_1V8: U_LDO_MGT1V0.3 (EN_UV), U_LDO_MGT1V2.3 (EN_UV), U_SEQ1.5 (FLAG2), U_VR_1V2.1 (EN), U_VR_1V8.1 (EN), U_VTT_0V6.7 (EN)
EN_2V5_3V3: U_SEQ1.4 (FLAG3), U_VR_2V5.1 (EN), U_VR_3V3.1 (EN)
ETH_MDI0_N: J_ETH.2, U_GBE.2 (MDI0_N)
ETH_MDI0_P: J_ETH.1, U_GBE.1 (MDI0_P)
ETH_MDI1_N: J_ETH.4, U_GBE.5 (MDI1_N)
ETH_MDI1_P: J_ETH.3, U_GBE.4 (MDI1_P)
EXT_AOM_CS_N: J_PORT_AOM_IL.6, U_ISO_AOM_IL.7 (B4)
EXT_AOM_RF_EN: J_PORT_AOM_IL.7, U_ISO_AOM_IL2.10 (B1)
EXT_AOM_SPI_MISO: J_PORT_AOM_IL.5, U_ISO_AOM_IL.8 (B3)
EXT_AOM_SPI_MOSI: J_PORT_AOM_IL.4, U_ISO_AOM_IL.9 (B2)
EXT_AOM_SPI_SCK: J_PORT_AOM_IL.3, U_ISO_AOM_IL.10 (B1)
EXT_BLK_CLK_N: J_PORT_BLK.6, U_ISO_BLK.7 (B4)
EXT_BLK_CLK_P: J_PORT_BLK.5, U_ISO_BLK.8 (B3)
EXT_BLK_SAFE_FORCE: J_PORT_BLK.8, U_ISO_BLK_CTRL.9 (B2)
EXT_BLK_START: J_PORT_BLK.7, U_ISO_BLK_CTRL.10 (B1)
EXT_BLK_TX_N: J_PORT_BLK.4, U_ISO_BLK.9 (B2)
EXT_BLK_TX_P: J_PORT_BLK.3, U_ISO_BLK.10 (B1)
EXT_HVDAC_CLRN: J_PORT_HVDAC.7, U_ISO_HVDAC2.10 (B1)
EXT_HVDAC_CSN: J_PORT_HVDAC.5, U_ISO_HVDAC.8 (B3)
EXT_HVDAC_LDAC_N: J_PORT_HVDAC.6, U_ISO_HVDAC.7 (B4)
EXT_HVDAC_MOSI: J_PORT_HVDAC.4, U_ISO_HVDAC.9 (B2)
EXT_HVDAC_SCLK: J_PORT_HVDAC.3, U_ISO_HVDAC.10 (B1)
EXT_IBIC_HIT_N: J_PORT_IBIC.4, U_ISO_IBIC.9 (B2)
EXT_IBIC_HIT_P: J_PORT_IBIC.3, U_ISO_IBIC.10 (B1)
EXT_IBIC_SPI_MOSI: J_PORT_IBIC.8, U_ISO_IBIC_SPI.9 (B2)
EXT_IBIC_SPI_SCK: J_PORT_IBIC.7, U_ISO_IBIC_SPI.10 (B1)
EXT_IBIC_TRIG_N: J_PORT_IBIC.6, U_ISO_IBIC.7 (B4)
EXT_IBIC_TRIG_P: J_PORT_IBIC.5, U_ISO_IBIC.8 (B3)
EXT_IL_CH_A_OK: J_PORT_AOM_IL.9, U_ISO_AOM_IL2.8 (B3)
EXT_IL_CH_B_OK: J_IL_1OO2D_AUX.1, U_ISO_IL_AUX.10 (B1)
EXT_IL_SAFE_EN: J_IL_1OO2D_AUX.2, U_ISO_IL_AUX.9 (B2)
EXT_IL_TRIP_OUT: J_PORT_AOM_IL.10, U_ISO_AOM_IL2.7 (B4)
EXT_IL_WDT_KICK: J_PORT_AOM_IL.8, U_ISO_AOM_IL2.9 (B2)
FB_1V2: R_FBB_1V2.1, R_FBT_1V2.2, U_VR_1V2.2 (VFB)
FB_1V8: R_FBB_1V8.1, R_FBT_1V8.2, U_VR_1V8.2 (VFB)
FB_2V5: R_FBB_2V5.1, R_FBT_2V5.2, U_VR_2V5.2 (VFB)
FB_3V3: R_FBB_3V3.1, R_FBT_3V3.2, U_VR_3V3.2 (VFB)
FMC_CLK_N: J_FMC_HPC.362 (CLK_N), R_TERM_FMC_CLK.2, U1.E8 (FMC_CLK_N)
FMC_CLK_P: J_FMC_HPC.361 (CLK_P), R_TERM_FMC_CLK.1, U1.E7 (FMC_CLK_P)
FMC_D0_N: J_FMC_HPC.366 (D0_N), R_TERM_FMC_D0.2, U1.E10 (FMC_D0_N)
FMC_D0_P: J_FMC_HPC.365 (D0_P), R_TERM_FMC_D0.1, U1.E9 (FMC_D0_P)
FMC_D1_N: J_FMC_HPC.370 (D1_N), R_TERM_FMC_D1.2, U1.F2 (FMC_D1_N)
FMC_D1_P: J_FMC_HPC.369 (D1_P), R_TERM_FMC_D1.1, U1.F1 (FMC_D1_P)
FMC_SPI_CSN: J_FMC_HPC.376 (SPI_CSN), U1.F4 (FMC_SPI_CSN)
FMC_SPI_SCK: J_FMC_HPC.375 (SPI_SCK), U1.F3 (FMC_SPI_SCK)
FPGA_DONE: R_DONE.1, U1.B7 (DONE_LED)
FPGA_INIT_B: R_INIT.2, U1.B8 (INIT_B)
GND: C_1V0_OUT.2, C_1V2_OUT.2, C_1V8_OUT.2, C_2V5_OUT.2, C_3V3_OUT.2, C_IN12_1.2, C_IN12_2.2, C_LF1.2, C_OUT_MGT0.2, C_OUT_MGT1.2, C_PDN_4U7_1.2, C_PDN_4U7_2.2, C_PDN_4U7_3.2, C_PDN_4U7_4.2, C_PDN_4U7_5.2, C_PDN_4U7_6.2, C_PDN_4U7_7.2, C_PDN_4U7_8.2, C_PDN_4U7_9.2, C_PDN_4U7_10.2, C_PDN_4U7_11.2, C_PDN_4U7_12.2, C_PDN_47U_1.2, C_PDN_47U_2.2, C_PDN_47U_3.2, C_PDN_47U_4.2, C_PDN_47U_5.2, C_PDN_47U_6.2, C_PDN_47U_7.2, C_PDN_47U_8.2, C_PDN_100N_1.2, C_PDN_100N_2.2, C_PDN_100N_3.2, C_PDN_100N_4.2, C_PDN_100N_5.2, C_PDN_100N_6.2, C_PDN_100N_7.2, C_PDN_100N_8.2, C_PDN_100N_9.2, C_PDN_100N_10.2, C_PDN_100N_11.2, C_PDN_100N_12.2, C_PDN_100N_13.2, C_PDN_100N_14.2, C_PDN_100N_15.2, C_PDN_100N_16.2, C_PDN_100N_17.2, C_PDN_100N_18.2, C_PDN_100N_19.2, C_PDN_100N_20.2, C_PDN_100N_21.2, C_PDN_100N_22.2, C_PDN_100N_23.2, C_PDN_100N_24.2, C_PDN_470N_1.2, C_PDN_470N_2.2, C_PDN_470N_3.2, C_PDN_470N_4.2, C_PDN_470N_5.2, C_PDN_470N_6.2, C_PDN_470N_7.2, C_PDN_470N_8.2, C_PDN_470N_9.2, C_PDN_470N_10.2, C_PDN_470N_11.2, C_PDN_470N_12.2, C_PDN_470N_13.2, C_PDN_470N_14.2, C_PDN_470N_15.2, C_PDN_470N_16.2, C_PDN_BULK1.2, C_PDN_BULK2.2, C_PDN_BULK3.2, C_PDN_BULK4.2, C_RST.2, C_SS_1V2.2, C_SS_1V8.2, C_SS_2V5.2, C_SS_3V3.2, C_STBY_3V3.2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
HVDAC_CLRN: U1.H1 (HVDAC_CLRN), U_ISO_HVDAC2.3 (A1)
HVDAC_CSN: U1.G9 (HVDAC_CSN), U_ISO_HVDAC.5 (A3)
HVDAC_LDAC_N: U1.G10 (HVDAC_LDAC_N), U_ISO_HVDAC.6 (A4)
HVDAC_MOSI: U1.G8 (HVDAC_MOSI), U_ISO_HVDAC.4 (A2)
HVDAC_SCLK: U1.G7 (HVDAC_SCLK), U_ISO_HVDAC.3 (A1)
IBIC_HIT_N: R_TERM_IBIC_HIT.2, U1.F6 (IBIC_HIT_N), U_ISO_IBIC.4 (A2)
IBIC_HIT_P: R_TERM_IBIC_HIT.1, U1.F5 (IBIC_HIT_P), U_ISO_IBIC.3 (A1)
IBIC_SPI_MOSI: U1.F10 (IBIC_SPI_MOSI), U_CLK.15 (SPI_MOSI), U_ISO_IBIC_SPI.4 (A2)
IBIC_SPI_SCK: U1.F9 (IBIC_SPI_SCK), U_CLK.14 (SPI_SCK), U_ISO_IBIC_SPI.3 (A1)
IBIC_TRIG_N: U1.F8 (IBIC_TRIG_N), U_ISO_IBIC.6 (A4)
IBIC_TRIG_P: U1.F7 (IBIC_TRIG_P), U_ISO_IBIC.5 (A3)
IL_CH_A_OK: U1.H8 (IL_CH_A_OK), U_ISO_AOM_IL2.5 (A3)
IL_CH_B_OK: U1.H9 (IL_CH_B_OK), U_ISO_IL_AUX.3 (A1)
IL_SAFE_EN: U1.K9 (IL_SAFE_EN), U_ISO_IL_AUX.4 (A2)
IL_TRIP_OUT: U1.H10 (IL_TRIP_OUT), U_ISO_AOM_IL2.6 (A4)
IL_WDT_KICK: U1.H7 (IL_WDT_KICK), U_ISO_AOM_IL2.4 (A2)
ISO_GND_AOM: J_IL_1OO2D_AUX.4, J_PORT_AOM_IL.2, J_PORT_AOM_IL.11, J_PORT_AOM_IL.12, U_ISO_AOM_IL.11 (GND2), U_ISO_AOM_IL2.11 (GND2), U_ISO_IL_AUX.7 (B4), U_ISO_IL_AUX.8 (B3), U_ISO_IL_AUX.11 (GND2)
ISO_GND_BLK: J_PORT_BLK.2, J_PORT_BLK.9, J_PORT_BLK.10, J_PORT_BLK.11, J_PORT_BLK.12, U_ISO_BLK.11 (GND2), U_ISO_BLK_CTRL.7 (B4), U_ISO_BLK_CTRL.8 (B3), U_ISO_BLK_CTRL.11 (GND2)
ISO_GND_HVDAC: J_PORT_HVDAC.2, J_PORT_HVDAC.8, J_PORT_HVDAC.9, J_PORT_HVDAC.10, J_PORT_HVDAC.11, J_PORT_HVDAC.12, U_ISO_HVDAC.11 (GND2), U_ISO_HVDAC2.7 (B4), U_ISO_HVDAC2.8 (B3), U_ISO_HVDAC2.9 (B2), U_ISO_HVDAC2.11 (GND2)
ISO_GND_IBIC: J_PORT_IBIC.2, J_PORT_IBIC.9, J_PORT_IBIC.10, J_PORT_IBIC.11, J_PORT_IBIC.12, U_ISO_IBIC.11 (GND2), U_ISO_IBIC_SPI.7 (B4), U_ISO_IBIC_SPI.8 (B3), U_ISO_IBIC_SPI.11 (GND2)
ISO_VDD_AOM: J_IL_1OO2D_AUX.3, J_PORT_AOM_IL.1, U_ISO_AOM_IL.12 (VDD2), U_ISO_AOM_IL2.12 (VDD2), U_ISO_IL_AUX.12 (VDD2)
ISO_VDD_BLK: J_PORT_BLK.1, U_ISO_BLK.12 (VDD2), U_ISO_BLK_CTRL.12 (VDD2)
ISO_VDD_HVDAC: J_PORT_HVDAC.1, U_ISO_HVDAC.12 (VDD2), U_ISO_HVDAC2.12 (VDD2)
ISO_VDD_IBIC: J_PORT_IBIC.1, U_ISO_IBIC.12 (VDD2), U_ISO_IBIC_SPI.12 (VDD2)
JTAG_TCK: J_JTAG.6 (TCK), U1.K5 (JTAG_TCK)
JTAG_TDI: J_JTAG.10 (TDI), U1.K7 (JTAG_TDI)
JTAG_TDO: J_JTAG.8 (TDO), U1.K8 (JTAG_TDO)
JTAG_TMS: J_JTAG.4 (TMS), U1.K6 (JTAG_TMS)
LED_DONE_A: D_DONE.1, R_DONE.2
MGTAVCC_1V0: C_OUT_MGT0.1, U1.A8 (MGTAVCC), U_LDO_MGT1V0.6 (PGFB), U_LDO_MGT1V0.9 (OUTS), U_LDO_MGT1V0.10 (OUT)
MGTAVTT_1V2: C_OUT_MGT1.1, U1.A9 (MGTAVTT), U_LDO_MGT1V2.6 (PGFB), U_LDO_MGT1V2.9 (OUTS), U_LDO_MGT1V2.10 (OUT)
PGOOD_ALL: R_PGOOD_PU.2, U1.B5 (PGOOD_ALL), U_LDO_MGT1V0.4 (PG), U_LDO_MGT1V2.4 (PG), U_VR_1V0.22 (PGOOD), U_VTT_0V6.9 (PGOOD)
PLL_CP1: R_LF1.1, U_CLK.10 (CP1_OUT)
PMBUS_SCL: U1.B9 (PMBUS_SCL), U_VR_1V0.25 (PMB_CLK)
PMBUS_SDA: U1.B10 (PMBUS_SDA), U_VR_1V0.26 (PMB_DATA)
QSPI_CLK: U1.E2 (QSPI_CLK), U_QSPI.6 (CLK)
QSPI_CS_N: U1.E1 (QSPI_CS_N), U_QSPI.1 (CS_N)
QSPI_D0: U1.E3 (QSPI_D0), U_QSPI.5 (D0)
QSPI_D1: U1.E4 (QSPI_D1), U_QSPI.2 (D1)
QSPI_D2: U1.E5 (QSPI_D2), U_QSPI.3 (D2)
QSPI_D3: U1.E6 (QSPI_D3), U_QSPI.7 (D3)
RGMII_RXC: U1.J7 (RGMII_RXC), U_GBE.25 (RXC)
RGMII_RXD0: U1.J9 (RGMII_RXD0), U_GBE.27 (RXD0)
RGMII_RXD1: U1.J10 (RGMII_RXD1), U_GBE.28 (RXD1)
RGMII_RXD2: U1.K1 (RGMII_RXD2), U_GBE.29 (RXD2)
RGMII_RXD3: U1.K2 (RGMII_RXD3), U_GBE.30 (RXD3)
RGMII_RX_CTL: U1.J8 (RGMII_RX_CTL), U_GBE.26 (RX_CTL)
RGMII_TXC: U1.J1 (RGMII_TXC), U_GBE.37 (TXC)
RGMII_TXD0: U1.J3 (RGMII_TXD0), U_GBE.39 (TXD0)
RGMII_TXD1: U1.J4 (RGMII_TXD1), U_GBE.40 (TXD1)
RGMII_TXD2: U1.J5 (RGMII_TXD2), U_GBE.41 (TXD2)
RGMII_TXD3: U1.J6 (RGMII_TXD3), U_GBE.42 (TXD3)
RGMII_TX_CTL: U1.J2 (RGMII_TX_CTL), U_GBE.38 (TX_CTL)
SEQ_EN: R_SEQ_EN.2, R_SEQ_EN_B.1, U_SEQ1.3 (EN)
SET_MGT0: R_SET_MGT0.1, U_LDO_MGT1V0.7 (SET)
SET_MGT1: R_SET_MGT1.1, U_LDO_MGT1V2.7 (SET)
SS_1V2: C_SS_1V2.1, U_VR_1V2.4 (SS)
SS_1V8: C_SS_1V8.1, U_VR_1V8.4 (SS)
SS_2V5: C_SS_2V5.1, U_VR_2V5.4 (SS)
SS_3V3: C_SS_3V3.1, U_VR_3V3.4 (SS)
SW_1V0: L_1V0.1, U_VR_1V0.10 (SW1), U_VR_1V0.11 (SW2)
SW_1V2: C_BST_1V2.2, L_1V2.1, U_VR_1V2.6 (SW)
SW_1V8: C_BST_1V8.2, L_1V8.1, U_VR_1V8.6 (SW)
SW_2V5: C_BST_2V5.2, L_2V5.1, U_VR_2V5.6 (SW)
SW_3V3: C_BST_3V3.2, L_3V3.1, U_VR_3V3.6 (SW)
SYS_RST_N: C_RST.1, R_RST.2, U1.B6 (SYS_RST_N)
UART_RX: U1.K4 (UART_RX), U_UART.13 (TXD)
UART_TX: U1.K3 (UART_TX), U_UART.14 (RXD)
USB_DM: J_USB.2, U_UART.7 (USB_DM)
USB_DP: J_USB.1, U_UART.8 (USB_DP)
VCCAUX_1V8: C_1V8_OUT.1, L_1V8.2, R_FBT_1V8.1, U1.A4 (VCCAUX), U_LDO_MGT1V0.1 (IN1), U_LDO_MGT1V0.2 (IN2), U_LDO_MGT1V2.1 (IN1), U_LDO_MGT1V2.2 (IN2), U_QSPI.8 (VCC)
VCCINT_1V0: C_1V0_OUT.1, C_PDN_4U7_1.1, C_PDN_4U7_2.1, C_PDN_4U7_3.1, C_PDN_4U7_4.1, C_PDN_4U7_5.1, C_PDN_4U7_6.1, C_PDN_4U7_7.1, C_PDN_4U7_8.1, C_PDN_4U7_9.1, C_PDN_4U7_10.1, C_PDN_4U7_11.1, C_PDN_4U7_12.1, C_PDN_47U_1.1, C_PDN_47U_2.1, C_PDN_47U_3.1, C_PDN_47U_4.1, C_PDN_47U_5.1, C_PDN_47U_6.1, C_PDN_47U_7.1, C_PDN_47U_8.1, C_PDN_100N_1.1, C_PDN_100N_2.1, C_PDN_100N_3.1, C_PDN_100N_4.1, C_PDN_100N_5.1, C_PDN_100N_6.1, C_PDN_100N_7.1, C_PDN_100N_8.1, C_PDN_100N_9.1, C_PDN_100N_10.1, C_PDN_100N_11.1, C_PDN_100N_12.1, C_PDN_100N_13.1, C_PDN_100N_14.1, C_PDN_100N_15.1, C_PDN_100N_16.1, C_PDN_100N_17.1, C_PDN_100N_18.1, C_PDN_100N_19.1, C_PDN_100N_20.1, C_PDN_100N_21.1, C_PDN_100N_22.1, C_PDN_100N_23.1, C_PDN_100N_24.1, C_PDN_470N_1.1, C_PDN_470N_2.1, C_PDN_470N_3.1, C_PDN_470N_4.1, C_PDN_470N_5.1, C_PDN_470N_6.1, C_PDN_470N_7.1, C_PDN_470N_8.1, C_PDN_470N_9.1, C_PDN_470N_10.1, C_PDN_470N_11.1, C_PDN_470N_12.1, C_PDN_470N_13.1, C_PDN_470N_14.1, C_PDN_470N_15.1, C_PDN_470N_16.1, C_PDN_BULK1.1, C_PDN_BULK2.1, C_PDN_BULK3.1, C_PDN_BULK4.1, L_1V0.2, U1.A1 (VCCINT_1), U1.A2 (VCCINT_2), U1.A3 (VCCINT_3), U_VR_1V0.15 (VOSNS_P)
VCCO_2V5_LVDS: C_2V5_OUT.1, J_JTAG.2 (VREF_2V5), L_2V5.2, R_FBT_2V5.1, U1.A6 (VCCO_2V5), U_CLK.48 (VCC_OUT)
VCCO_3V3_IO: C_3V3_OUT.1, J_ETH.5, J_FMC_HPC.1 (V3P3), J_USB.3, L_3V3.2, R_FBT_3V3.1, R_INIT.1, R_RST.1, U1.A7 (VCCO_3V3), U_CLK.1 (VCC1), U_GBE.10 (VDD33_1), U_GBE.46 (VDD33_2), U_ISO_AOM_IL.1 (VDD1), U_ISO_AOM_IL2.1 (VDD1), U_ISO_BLK.1 (VDD1), U_ISO_BLK_CTRL.1 (VDD1), U_ISO_HVDAC.1 (VDD1), U_ISO_HVDAC2.1 (VDD1), U_ISO_IBIC.1 (VDD1), U_ISO_IBIC_SPI.1 (VDD1), U_ISO_IL_AUX.1 (VDD1), U_UART.3 (V3P3_1), U_UART.31 (V3P3_2), U_VTT_0V6.10 (VIN), Y_VCXO.4 (VDD)
VCXO_100M: U_CLK.7 (OSCIN_100M), Y_VCXO.3 (OUT_100M)
VCXO_VCTRL: C_LF1.1, R_LF1.2, Y_VCXO.1 (VCTRL)
VDD_1V2_DDR: C_1V2_OUT.1, L_1V2.2, R_FBT_1V2.1, R_VTT_REFIN_T.1, U1.A5 (VCCO_1V2), U_DDR4_A.1 (VDD1), U_DDR4_A.91 (VDD2), U_DDR4_B.1 (VDD1), U_DDR4_B.91 (VDD2), U_VTT_0V6.2 (VLDOIN)
VIN_12V: C_IN12_1.1, C_IN12_2.1, D_TVS1.1, F1.2, J_FMC_HPC.2 (V12P0), R_SEQ_EN.1, U_LDO_STBY_3V3.1 (VIN), U_LDO_STBY_3V3.3 (EN), U_VR_1V0.1 (VIN1), U_VR_1V0.2 (VIN2), U_VR_1V0.35 (VIN3), U_VR_1V2.8 (VIN), U_VR_1V8.8 (VIN), U_VR_2V5.8 (VIN), U_VR_3V3.8 (VIN)
VIN_12V_RAW: F1.1, J_PWR12V.1 (V12_A), J_PWR12V.2 (V12_B)
VR5_1V2: C_VR5_1V2.1, U_VR_1V2.3 (VREG5)
VR5_1V8: C_VR5_1V8.1, U_VR_1V8.3 (VREG5)
VR5_2V5: C_VR5_2V5.1, U_VR_2V5.3 (VREG5)
VR5_3V3: C_VR5_3V3.1, U_VR_3V3.3 (VREG5)
VTT_0V6_DDR: C_VTT_OUT.1, R_DDR_VTT1.2, R_DDR_VTT2.2, U_VTT_0V6.3 (VO), U_VTT_0V6.5 (VOSNS)
VTT_REFIN_0V6: R_VTT_REFIN_B.1, R_VTT_REFIN_T.2, U_VTT_0V6.1 (REFIN)
V_3V3_STBY: C_STBY_3V3.1, R_PGOOD_PU.1, U_LDO_STBY_3V3.4 (SENSE), U_LDO_STBY_3V3.5 (VOUT), U_SEQ1.1 (VCC)
WR_TRIG_50: J_WR_TRIG.1 (WR_TRIG), R_WR_50.1, U1.C7 (WR_TRIG_IN), U_CLK.12 (SYNC_WR)
